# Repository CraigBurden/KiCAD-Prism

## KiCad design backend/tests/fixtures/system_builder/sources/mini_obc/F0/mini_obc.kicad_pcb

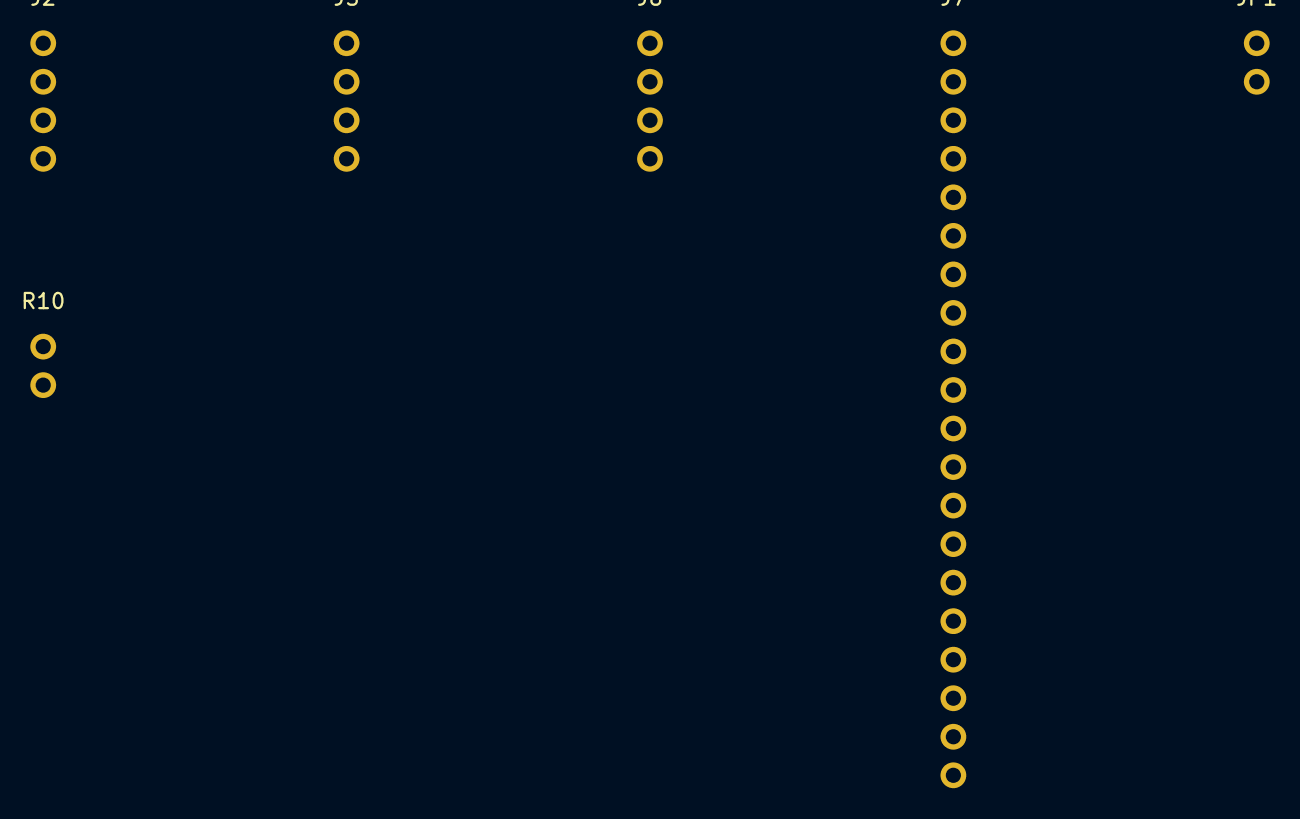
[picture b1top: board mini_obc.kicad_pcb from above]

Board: 2 copper layers, 6 parts (0 on the bottom side), 6 nets, no tracks yet.

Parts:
J2, J5, J6: Conn_01x04; PinHeader_1x04_P2.54mm_Vertical
J7: Conn_02x10; PinHeader_2x10_P2.54mm_Vertical
JP1: SolderJumper_2_Open; SolderJumper-2_P1.3mm_Open_Pad1.0x1.5mm
R10: R; R_0603_1608Metric

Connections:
+3V3: J7.7, J7.8, R10.2
/PWR_EN: J2.4, JP1.1
/PWR_GOOD: J2.3, J6.3
GND: J2.2, J5.2, J6.2, J7.1, J7.2, JP1.2
PAYLOAD_RESET#: J7.17, R10.1
VIN_28V: J2.1, J5.1, J6.1

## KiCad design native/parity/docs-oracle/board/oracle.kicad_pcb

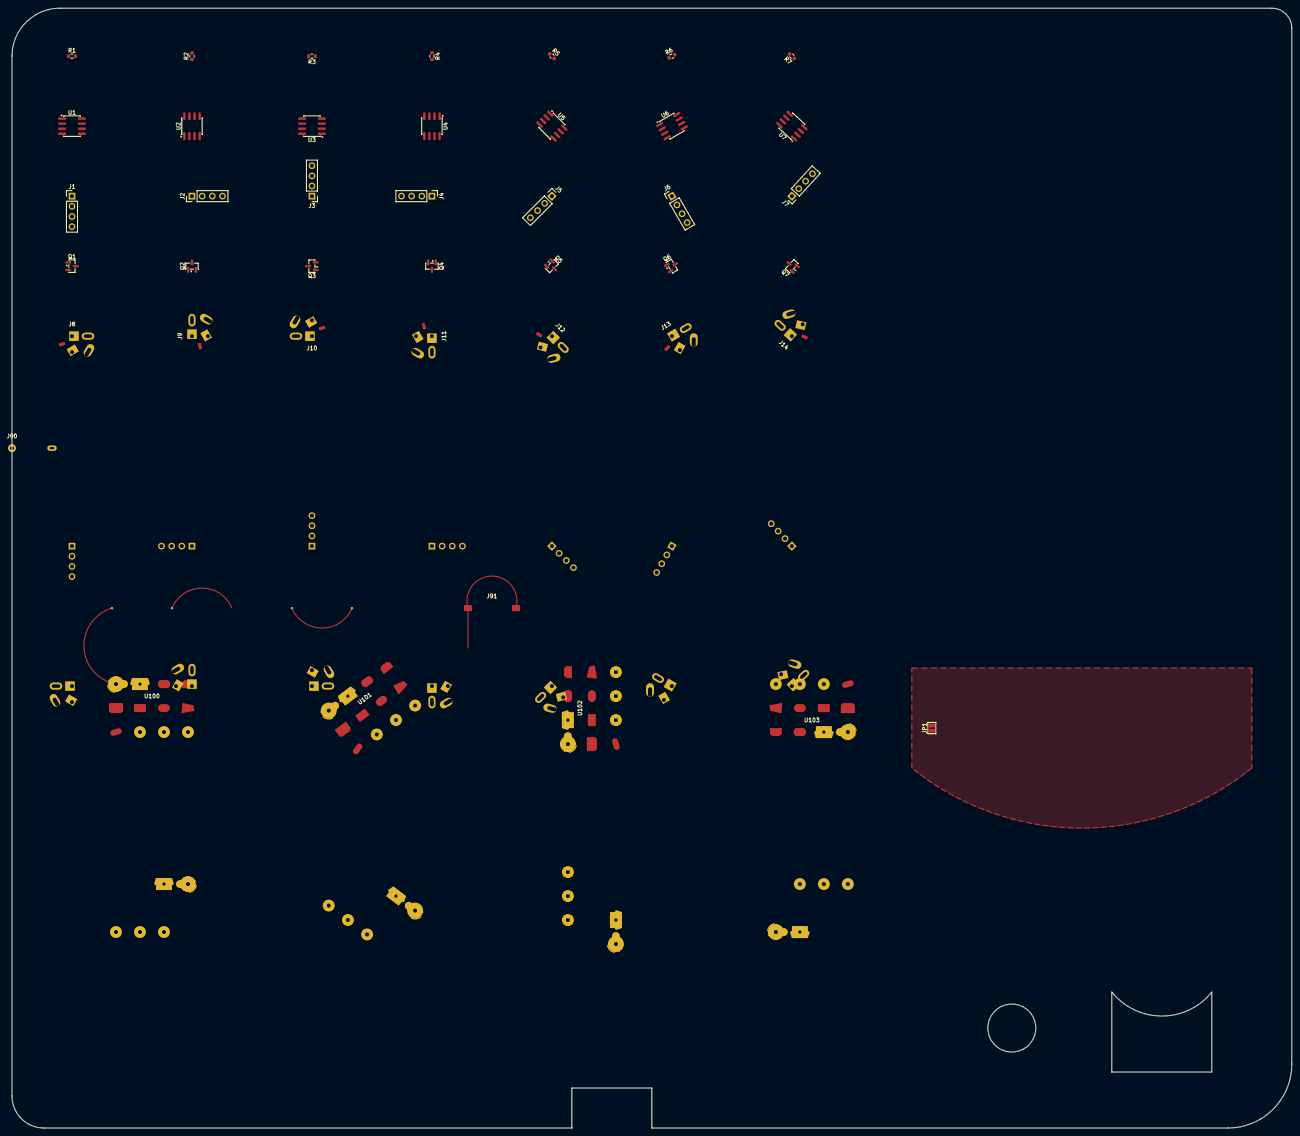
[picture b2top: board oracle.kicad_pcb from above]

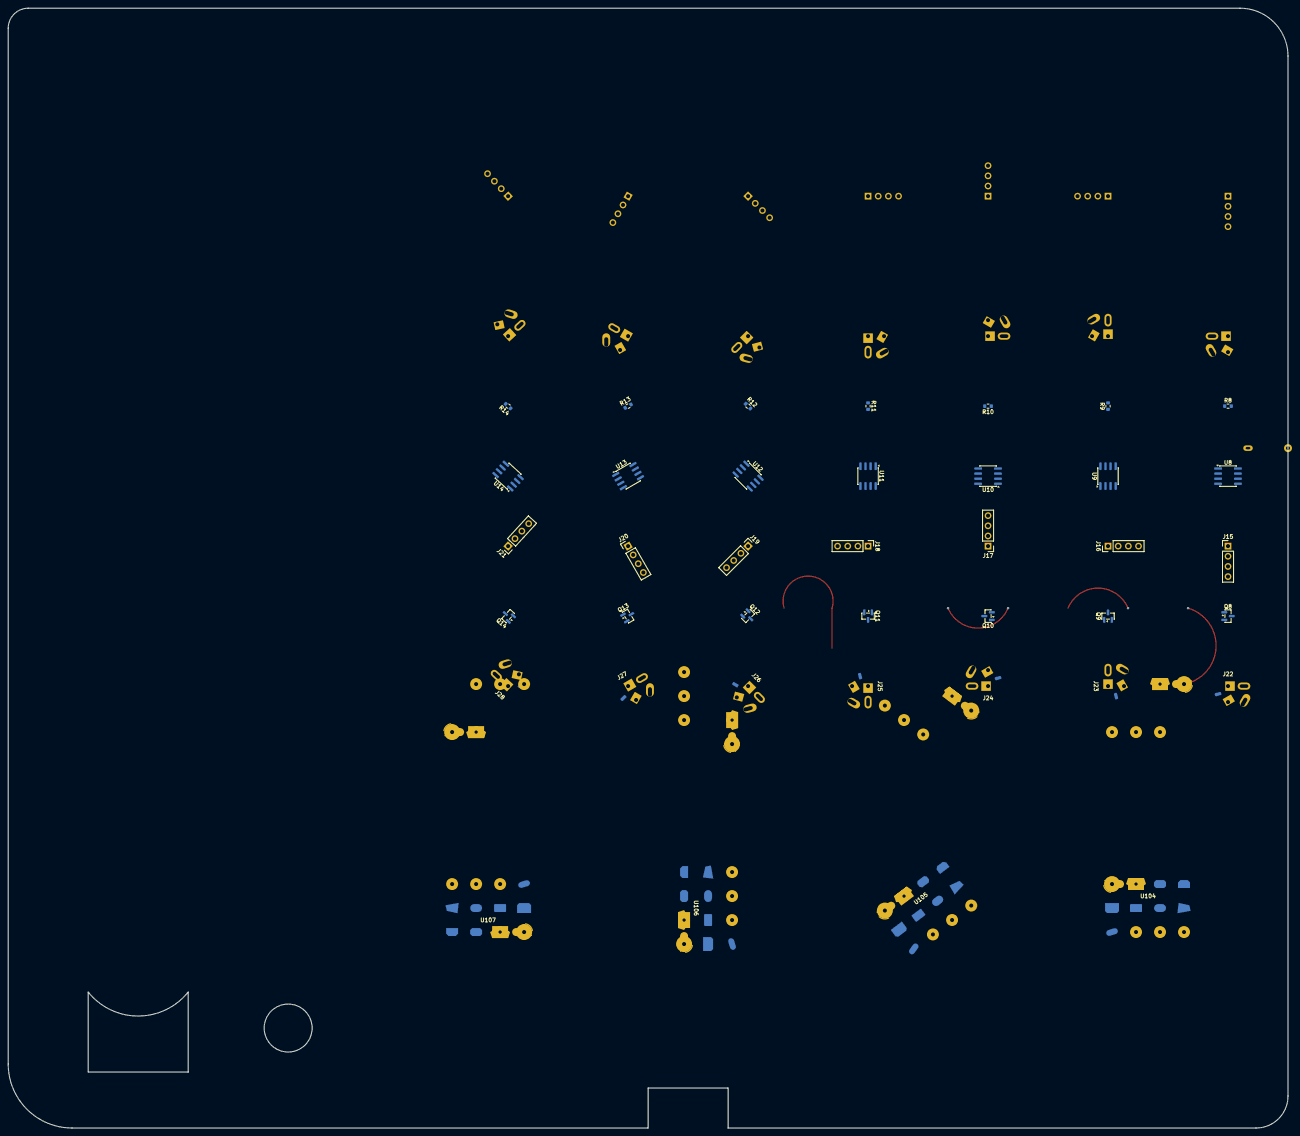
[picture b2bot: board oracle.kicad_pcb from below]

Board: 4 copper layers, 320.0 x 280.0 mm, 81 parts (39 on the bottom side), 3 nets.

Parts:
J1, J2, J3, J4, J5, J6, J7, J15, J16, J17, J18, J19, J20, J21: PinHeader_1x04_P2.54mm_Vertical
J8, J9, J10, J11, J12, J13, J14, J22, J23, J24, J25, J26, J27, J28: OffsetDrills
J90: EdgePads
J91: ArcLink
JP1: SolderJumper-2_P1.3mm_Open_Pad1.0x1.5mm
Q1, Q2, Q3, Q4, Q5, Q6, Q7, Q8, Q9, Q10, Q11, Q12, Q13, Q14: SOT-23
R1, R2, R3, R4, R5, R6, R7, R8, R9, R10, R11, R12, R13, R14: R_0603_1608Metric
U1, U2, U3, U4, U5, U6, U7, U8, U9, U10, U11, U12, U13, U14: SOIC-8_3.9x4.9mm_P1.27mm
U100, U101, U102, U103, U104, U105, U106, U107: UnusualPads

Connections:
GND: J90.1, U100.1, U101.1, U102.1, U103.1, U104.1, U105.1, U106.1, U107.1
SIG_LINK: J91.1, J91.2
VCC: J90.2, U100.2, U100.10, U101.2, U101.10, U102.2, U102.10, U103.2, U103.10, U104.2, U104.10, U105.2, U105.10, U106.2, U106.10, U107.2, U107.10
